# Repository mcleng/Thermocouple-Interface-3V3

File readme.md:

Thermocouple Interface | 3.3V
=============================

This work is licensed under a <a rel="license" href="http://creativecommons.org/licenses/by-sa/3.0/">Creative Commons Attribution-ShareAlike 3.0 Unported License</a>.

Designed By:

*	Ryan McLaughlin <ryan@ryanjmclaughlin.com>

Summary
-------

The single thermocouple interface was made out of the need to interface a micro controller to a thermocouple. One of the popular chips to perform a thermocouple to digital conversion is the MAX6675 (now MAX31855). While this is a great little chip it is a small surface mount part and therefore difficult to solder. The thermocouple interface board not only helps with having the chip broken out to a simple 0.1" header, but also provides a mini-thermocouple connector to easily interface to a thermocouple. Thermocouples are not designed to be soldered and this provides a good solid connection, while also using the proper metals in the connector required for a thermocouple connection.

**CAUTION: The MAX31855 is for 3.3V only! If connecting to a 5V system, you must use a level shifter!!**

Tutorial
--------

It is simple to get everything up and running.

1.	Install a header or solder jumper wires to the pin connections
2.	Connect a K-Type [Thermocouple](http://en.wikipedia.org/wiki/Thermocouple Thermocouple) to the PCB Thermocouple Connector use a Thermocouple Wire Connector if necessary
3.	Wire the necessary connections to an Arduino or other micro controller, the bare minimum connections are +V, GND, SCK, SO, CS  **CAUTION: The MAX31855 is for 3.3V only! If connecting to a 5V system, you must use a level shifter!!**
4.	If using an Arduino, load one of the samples from the MAX6675 Arduino Library and you should see temperature information in the serial console. With other micro controllers you can access the chip using a standard SPI interface. See MAX31855 data sheet for more details.

Board Specs
-----------

*	Dimensions: 1.25" x 1.50"
*	Chip: MAX31855
*	Voltage: 3.3V
*	Header: 1x6 0.1" Pitch
*	Fixturing: Four Corner Holes (1.20"x0.95" Spacing)

Versions
--------

###Version 1.3

* Initial release under Eagle 6.1 on Github
* PCB Production dates: 09-2011, 01-2012

This revision changed from the MAX6675 to the new MAX31855 chip.  It has more accuracy and a better temperature range.  The footprint and fixturing holes have remained the same, but the board layout modified to make a better connection between the thermocouple connector and the MAX31855.  They were move closer together and larger traces between the chip and connector.  This should allow for better CJC, and more accuracy.  The board comes fully assembled along with a male and female header, and a 4050 level shifter chip. <small>Licensed under OSHW</small>

####Board Specs
*	Dimensions: 1.25" x 1.50"
*	Chip: MAX31855
*	Voltage: 3.3V
*	Header: 1x6 0.1" Pitch
*	Fixturing: Four Corner Holes (1.20"x0.95" Spacing)

###Version 1.2

This version of the board did not make many changes from V1.1.  The changes were mainly related to the manufacturing.  The PCB dimensions were better specified in the gerber files sent to fab resulting in better board routing.  The previous version was router slightly smaller than specified.  The solder mask was also updated to correct for some errors and spacing.

####Board Specs
*	Dimensions: 1.25" x 1.50"
*	Chip: MAX6675
*	Header: 1x6 0.1" Pitch
*	Fixturing: Four Corner Holes (1.20"x0.95" Spacing)

###Version 1.1

The next version made some major changes based on some feedback of the original version.  The additions included:

*	The recommended 0.1µF filtering cap for the MAX6675
*	Additional fixturing holes in each corner of the board to allow for flexible and rigid mounting
*	A power indicator LED
*	A status indicator LED that is driven by a separate pin, which is useful for displaying a status of the thermocouple from your program

####Board Specs
*	Dimensions: 1.25" x 1.50"
*	Chip: MAX6675
*	Header: 1x6 0.1" Pitch
*	Fixturing: Four Corner Holes (1.20"x0.95" Spacing)

###Version 1.0

The original version of this board was built as a simple breakout interface for the MAX6675.  The first attempt to do this was using a [http://www.sparkfun.com/commerce/product_info.php?products_id=494 SOIC to DIP adapter board].  While this worked, it did not provide a reliable connection for a thermocouple.  The solution was to use a [[PCB Thermocouple Connector]].

####Board Specs
*	Dimensions: 2.00" x 0.75"
*	Chip: MAX6675
*	Header: 1x5 0.1" Pitch
*	Fixturing: Single Hole

Purchase
--------

[store.ryanjmclaughlin.com](http://store.ryanjmclaughlin.com). 

TODO
----

*	Do not route LED through level shifter

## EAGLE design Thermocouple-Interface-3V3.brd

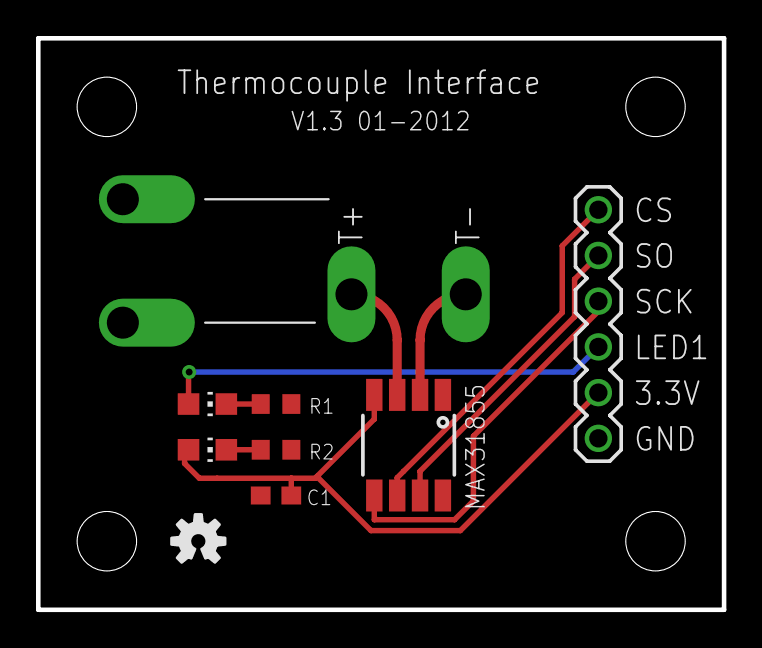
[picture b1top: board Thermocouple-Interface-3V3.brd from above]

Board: 2 copper layers, 38.1 x 31.8 mm, 13 parts (0 on the bottom side), 10 nets.

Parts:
C1: 0.1µF; C0603
JP1: I/O; 1X06
LED1: Status; CHIP-LED0805
LED2: Power; CHIP-LED0805
R1: 140; R0603
R2: 150; R0603
TC1: TC_JACK
U1: MAX31855; SOIC-8
U$1, U$2, U$3, U$4: STAND-OFF
U$5: OSHW-LOGO-S

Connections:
CS: JP1.1, U1.CS
GND: C1.2, JP1.6, R1.1, R2.1, TC1.P$1, TC1.P$2, U1.GND
LED1: JP1.4, LED1.A
unnamed: LED1.C, R1.2
unnamed: LED2.C, R2.2
SCK: JP1.3, U1.SCK
SO: JP1.2, U1.SO
T+: TC1.T+, U1.T+
T-: TC1.T-, U1.T-
VCC: C1.1, JP1.5, LED2.A, U1.VCC

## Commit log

2012-01-29 Initial release to github, v1.3
2012-01-29 Updated for 01-2012 pcb production
2012-01-31 Added schematic and board images/pdf

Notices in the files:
readme.md:
CC BY-SA 3.0
